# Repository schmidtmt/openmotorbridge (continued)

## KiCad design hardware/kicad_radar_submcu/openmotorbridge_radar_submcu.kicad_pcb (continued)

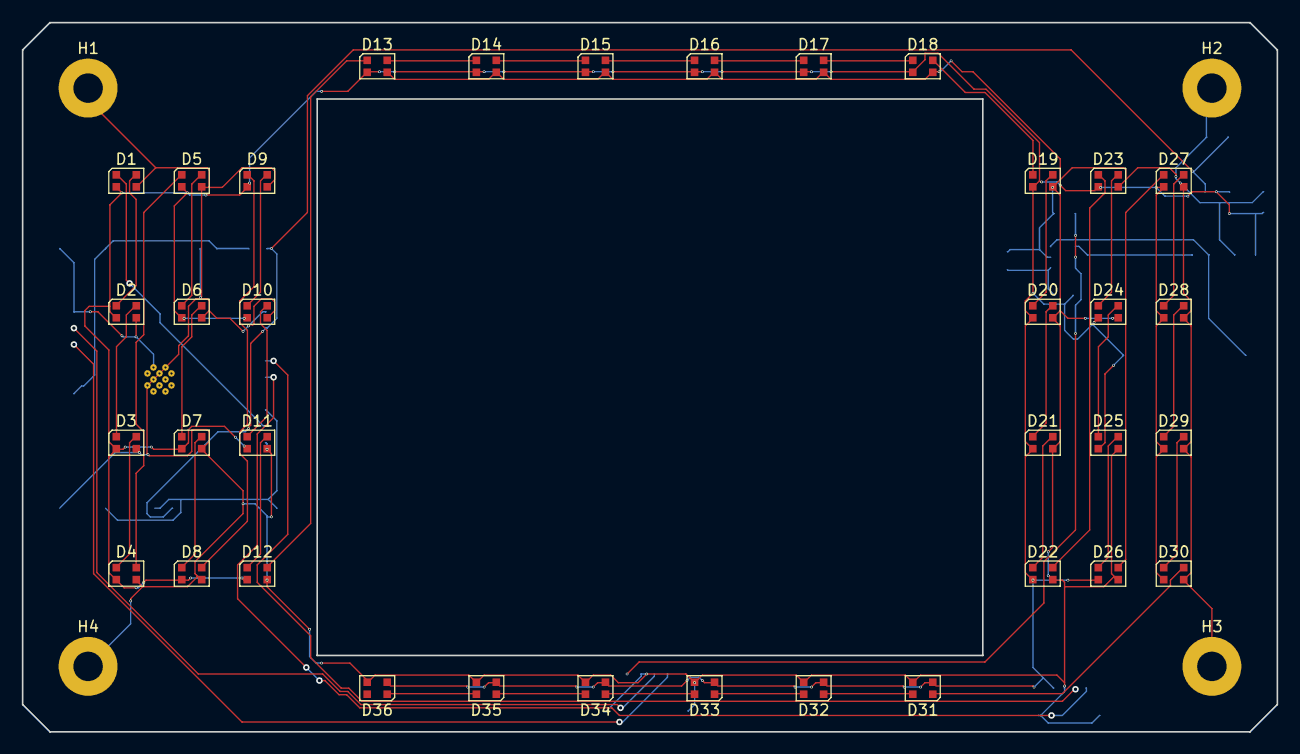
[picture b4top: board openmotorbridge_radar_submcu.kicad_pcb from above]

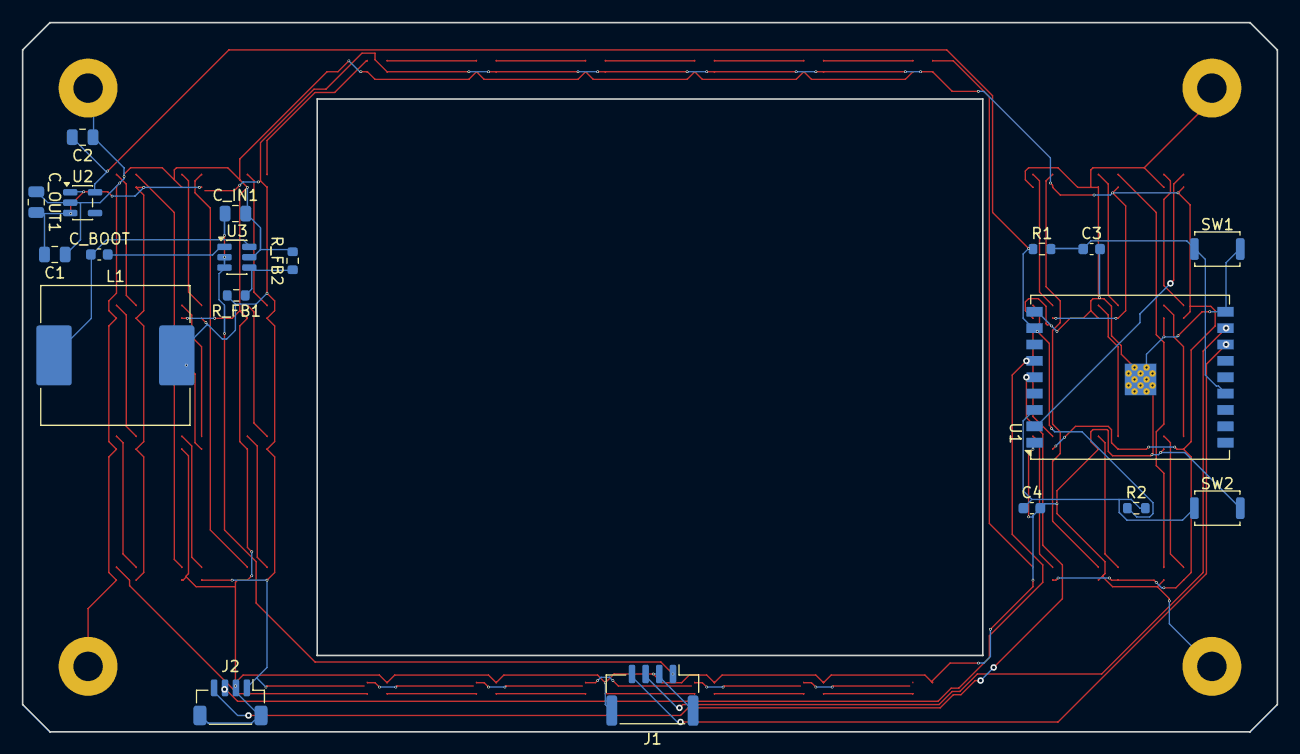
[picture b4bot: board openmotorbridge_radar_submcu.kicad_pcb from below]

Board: 2 copper layers, 115.0 x 65.0 mm, 59 parts (19 on the bottom side), 49 nets.

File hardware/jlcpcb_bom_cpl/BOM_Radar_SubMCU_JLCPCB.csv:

Designator,Comment,Footprint,LCSC Part #,Quantity
C1,10uF_16V,C_0805_2012Metric,,1
C2,10uF_10V,C_0805_2012Metric,,1
"C3, C4",100nF,C_0603_1608Metric,,2
D25,PESD5V0S2BT,SOT-23,,1
"D1, D10, D11, D12, D13, D14, D15, D16, D17, D18, D19, D2, D20, D21, D22, D23, D24, D25, D26, D27, D28, D29, D3, D30, D31, D32, D33, D34, D35, D36, D4, D5, D6, D7, D8, D9",WS2812B-2020,LED_WS2812B-2020_PLCC4_2.0x2.0mm,,36
"H1, H2, H3, H4",M2.5_MountingHole,MountingHole_2.7mm_M2.5_Pad,,4
J1,JST_SH_4P_CENTRAL,JST_SH_SM04B-SRSS-TB_1x04-1MP_P1.00mm_Horizontal,,1
J2,JST_SH_4P_MR20,JST_SH_SM04B-SRSS-TB_1x04-1MP_P1.00mm_Horizontal,,1
J3,U.FL_5G9_V2X,U.FL_Hirose_U.FL-R-SMT-1_Vertical,,1
"R1, R2",10k,R_0603_1608Metric,,2
SW1,BOOT_SW,SW_Push_SPST_NO_Alps_SKRK,,1
SW2,RESET_SW,SW_Push_SPST_NO_Alps_SKRK,,1
U1,ESP32-C5-WROOM-1U,ESP32-C3-WROOM-02U,,1
U2,TPS7A0533,SOT-23-5,,1

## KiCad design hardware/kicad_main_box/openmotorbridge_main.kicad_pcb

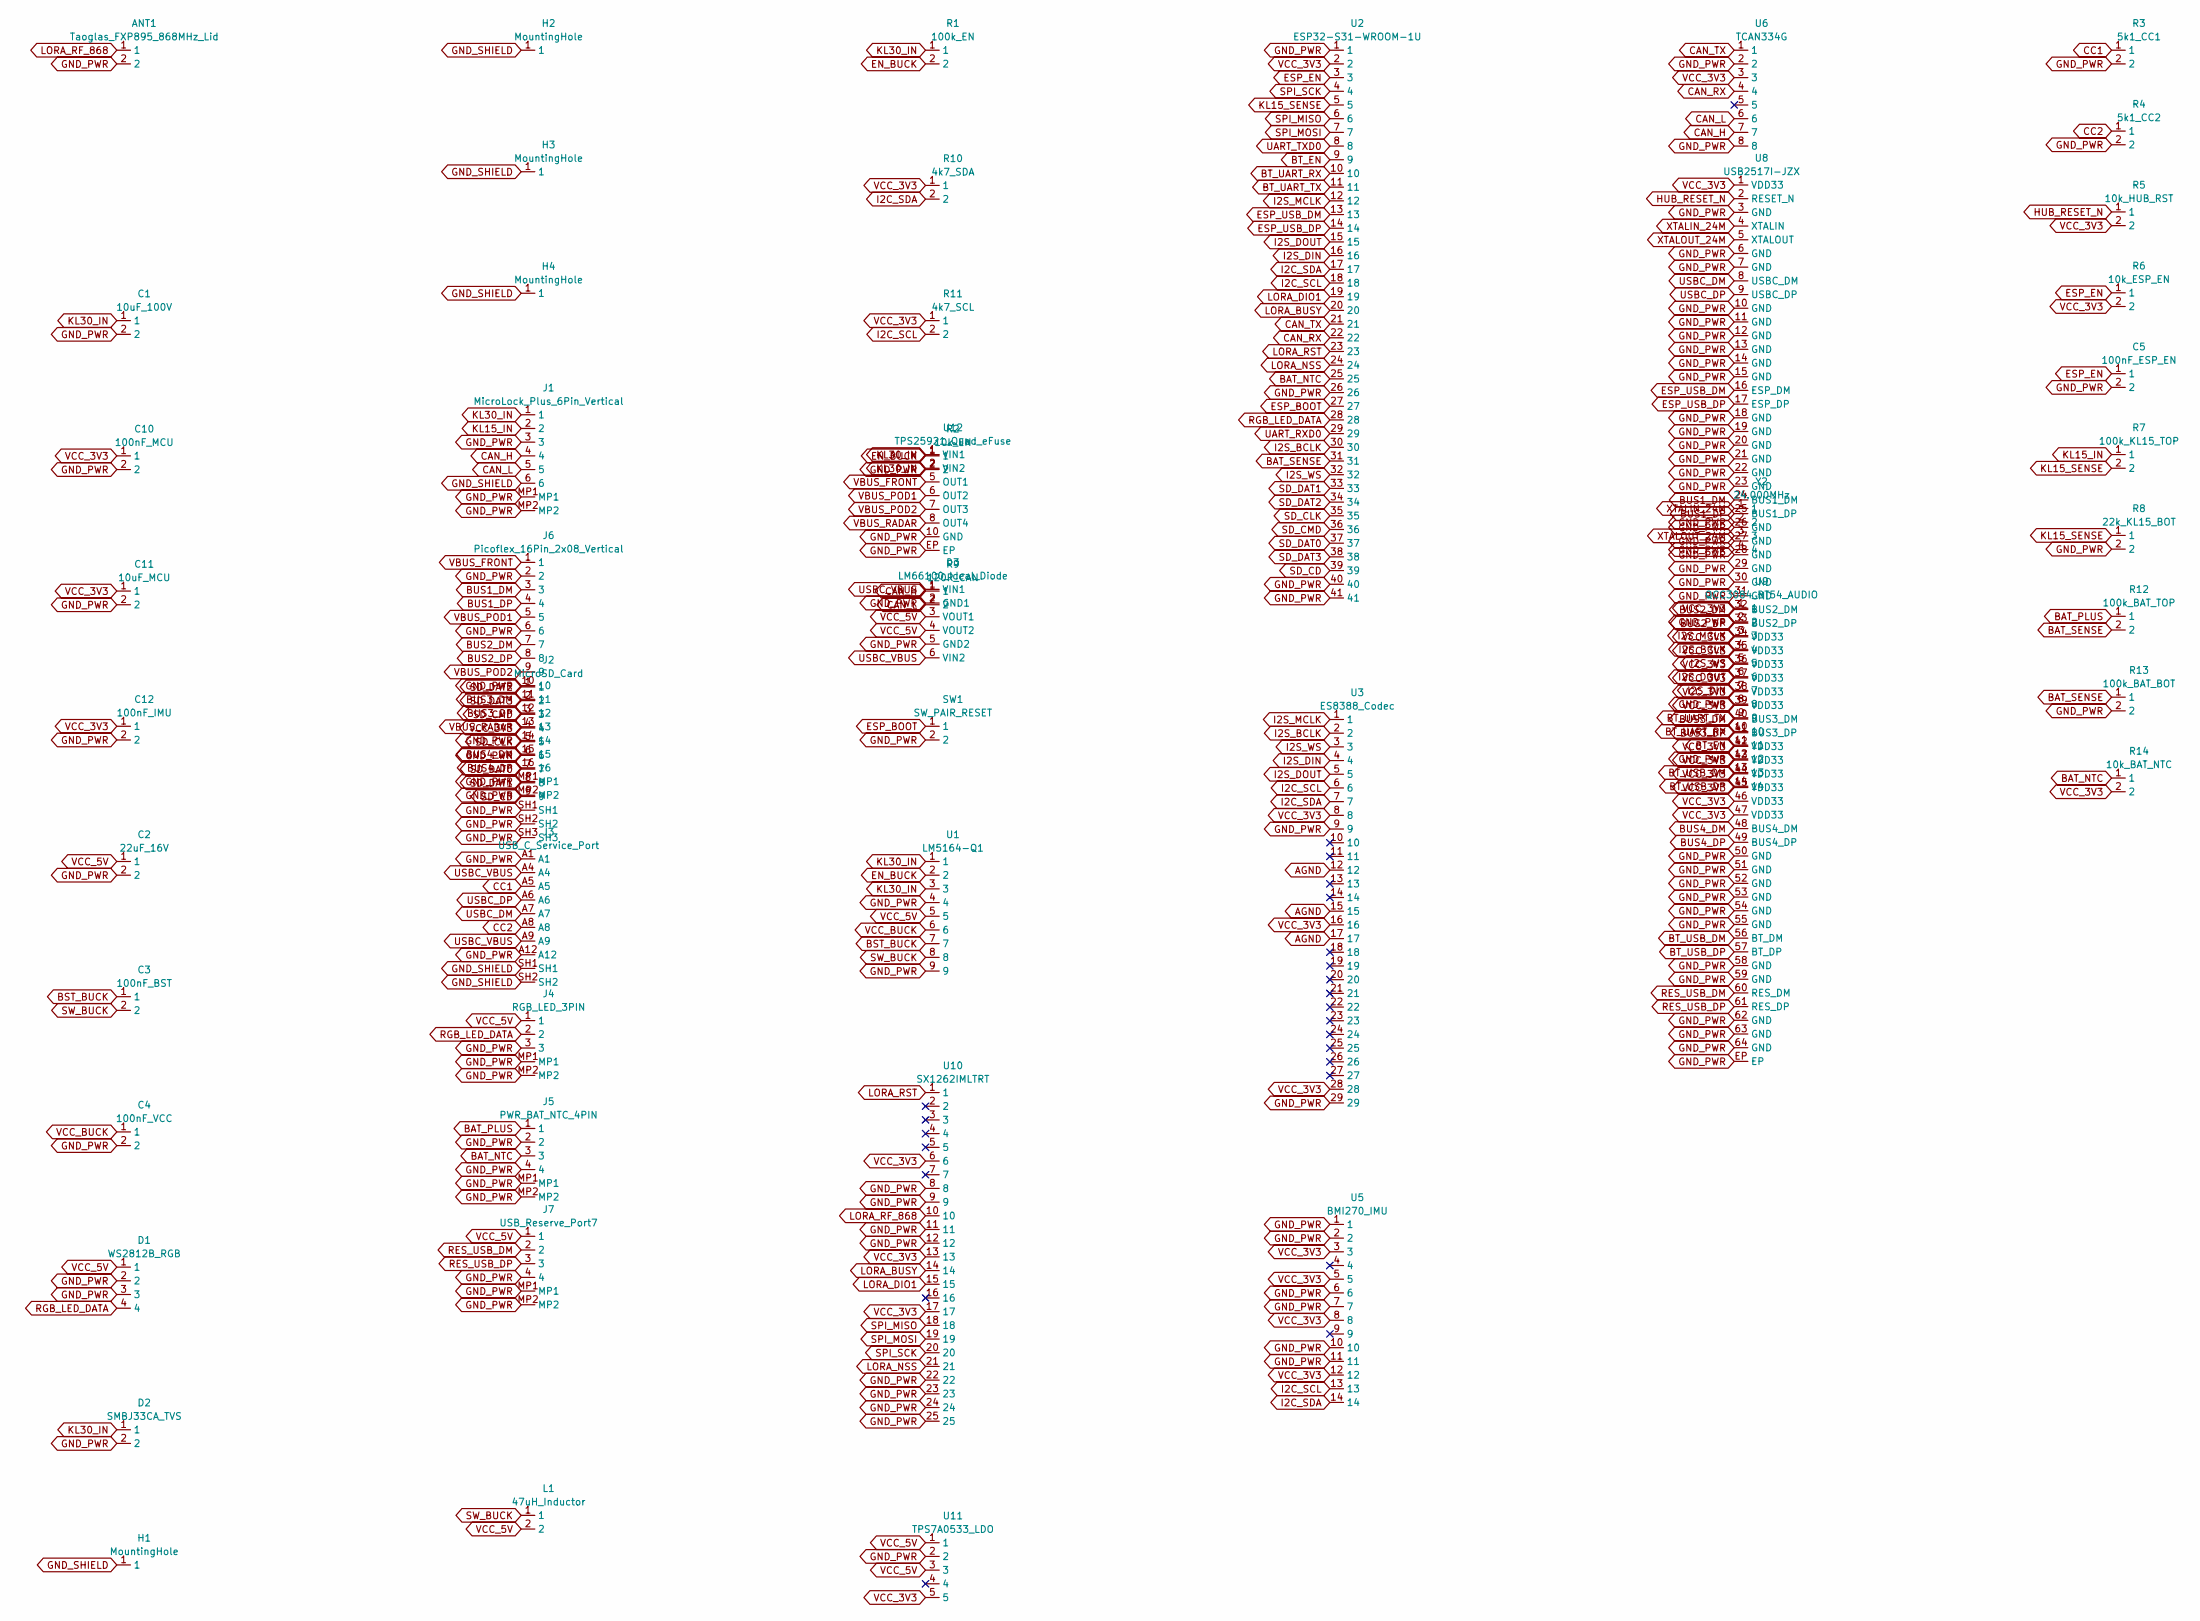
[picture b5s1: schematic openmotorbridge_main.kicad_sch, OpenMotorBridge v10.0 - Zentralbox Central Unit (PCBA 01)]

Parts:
ANT1: Taoglas_FXP895_868MHz_Lid; U.FL_Hirose_U.FL-R-SMT-1_Vertical
C1: 10uF_100V; C_0805_2012Metric
C2: 22uF_16V; C_0805_2012Metric
C3: 100nF_BST; C_0603_1608Metric
C4: 100nF_VCC; C_0603_1608Metric
C5: 100nF_ESP_EN; C_0603_1608Metric
C10: 100nF_MCU; C_0603_1608Metric
C11: 10uF_MCU; C_0805_2012Metric
C12: 100nF_IMU; C_0603_1608Metric
D1: WS2812B_RGB; LED_WS2812B-2020
D2: SMBJ33CA_TVS; D_SMB
D3: LM66100_Ideal_Diode; SOT-23-6
H1, H2, H3, H4: MountingHole; MountingHole_3.2mm_M3_Pad_Via
J1: MicroLock_Plus_6Pin_Vertical; Molex_Micro-Lock_Plus_505568-0671_1x06_P1.25mm_Vertical
J2: MicroSD_Card; microSD_HC_Hirose_DM3D-SF
J3: USB_C_Service_Port; USB_C_Receptacle_HRO_TYPE-C-31-M-12_16P
J4: RGB_LED_3PIN; Molex_Micro-Lock_Plus_505568-0371_1x03_P1.25mm_Vertical
J5: PWR_BAT_NTC_4PIN; Molex_Micro-Lock_Plus_505568-0471_1x04_P1.25mm_Vertical
J6: Picoflex_16Pin_2x08_Vertical; Molex_Picoflex_90814-0016_2x08_P1.27mm_Vertical
J7: USB_Reserve_Port7; Molex_Micro-Lock_Plus_505568-0471_1x04_P1.25mm_Vertical
L1: 47uH_Inductor; L_Sunlord_MWSA1206S-470
R1: 100k_EN; R_0603_1608Metric
R2: 10k_EN; R_0603_1608Metric
R3: 5k1_CC1; R_0603_1608Metric
R4: 5k1_CC2; R_0603_1608Metric
R5: 10k_HUB_RST; R_0603_1608Metric
R6: 10k_ESP_EN; R_0603_1608Metric
R7: 100k_KL15_TOP; R_0603_1608Metric
R8: 22k_KL15_BOT; R_0603_1608Metric
R9: 120R_CAN; R_0603_1608Metric
R10: 4k7_SDA; R_0603_1608Metric
R11: 4k7_SCL; R_0603_1608Metric
R12: 100k_BAT_TOP; R_0603_1608Metric
R13: 100k_BAT_BOT; R_0603_1608Metric
R14: 10k_BAT_NTC; R_0603_1608Metric
SW1: SW_PAIR_RESET; SW_Push_SPST_NO_Alps_SKRK
U1: LM5164-Q1; SOIC-8-1EP_3.9x4.9mm_P1.27mm_EP2.41x3.3mm
U2: ESP32-S31-WROOM-1U; ESP32-S3-WROOM-1U
U3: ES8388_Codec; QFN-28-1EP_4x4mm_P0.4mm_EP2.4x2.4mm
U5: BMI270_IMU; LGA-14_2.5x3mm_P0.5mm
U6: TCAN334G; SOIC-8_3.9x4.9mm_P1.27mm
U8: USB2517I-JZX; QFN-64-1EP_9x9mm_P0.5mm_EP7.15x7.15mm
U9: QCC3084_BT54_AUDIO; Qualcomm_QCC3084_Module
U10: SX1262IMLTRT; QFN-24-1EP_4x4mm_P0.5mm_EP2.8x2.8mm
U11: TPS7A0533_LDO; SOT-23-5
U12: TPS25921_Quad_eFuse; QFN-20-1EP_3.5x4mm_P0.5mm
Y2: 24.000MHz; Crystal_SMD_2016-4Pin_2.0x1.6mm

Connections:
AGND: U3.12, U3.15, U3.17
BAT_NTC: J5.3, R14.1, U2.25
BAT_PLUS: J5.1, R12.1
BAT_SENSE: R12.2, R13.1, U2.31
BST_BUCK: C3.1, U1.7
BT_EN: U2.9, U9.11
BT_UART_RX: U2.10, U9.10
BT_UART_TX: U2.11, U9.9
BT_USB_DM: U8.56 (BT_DM), U9.13
BT_USB_DP: U8.57 (BT_DP), U9.14
BUS1_DM: J6.3, U8.24 (BUS1_DM)
BUS1_DP: J6.4, U8.25 (BUS1_DP)
BUS2_DM: J6.7, U8.32 (BUS2_DM)
BUS2_DP: J6.8, U8.33 (BUS2_DP)
BUS3_DM: J6.11, U8.40 (BUS3_DM)
BUS3_DP: J6.12, U8.41 (BUS3_DP)
BUS4_DM: J6.15, U8.48 (BUS4_DM)
BUS4_DP: J6.16, U8.49 (BUS4_DP)
CAN_H: J1.4, R9.1, U6.7
CAN_L: J1.5, R9.2, U6.6
CAN_RX: U2.22, U6.4
CAN_TX: U2.21, U6.1
CC1: J3.A5, R3.1
CC2: J3.A8, R4.1
EN_BUCK: R1.2, R2.1, U1.2
ESP_BOOT: SW1.1, U2.27
ESP_EN: C5.1, R6.1, U2.3
ESP_USB_DM: U2.13, U8.16 (ESP_DM)
ESP_USB_DP: U2.14, U8.17 (ESP_DP)
GND_PWR: ANT1.2, C1.2, C2.2, C4.2, C5.2, C10.2, C11.2, C12.2, D1.2, D1.3, D2.2, D3.2 (GND1), D3.5 (GND2), J1.3, J1.MP1, J1.MP2, J2.6, J2.SH1, J2.SH2, J2.SH3, J3.A1, J3.A12, J4.3, J4.MP1, J4.MP2, J5.2, J5.4, J5.MP1, J5.MP2, J6.2, J6.6, J6.10, J6.14, J6.MP1, J6.MP2, J7.4, J7.MP1, J7.MP2, R2.2, R3.2, R4.2, R8.2, R13.2, SW1.2, U1.4, U1.9, U2.1, U2.26, U2.40, U2.41, U3.9, U3.29, U5.1, U5.2, U5.6, U5.7, U5.10, U5.11, U6.2, U6.8, U8.3 (GND), U8.6 (GND), U8.7 (GND), U8.10 (GND), U8.11 (GND), U8.12 (GND), U8.13 (GND), U8.14 (GND), U8.15 (GND), U8.18 (GND), U8.19 (GND), U8.20 (GND), U8.21 (GND), U8.22 (GND), U8.23 (GND), U8.26 (GND), U8.27 (GND), U8.28 (GND), U8.29 (GND), U8.30 (GND), U8.31 (GND), U8.50 (GND), U8.51 (GND), U8.52 (GND), U8.53 (GND), U8.54 (GND), U8.55 (GND), U8.58 (GND), U8.59 (GND), U8.62 (GND), U8.63 (GND), U8.64 (GND), U8.EP, U9.2, U9.8, U9.12, U10.8, U10.9, U10.11, U10.12, U10.22, U10.23, U10.24, U10.25, U11.2, U12.10 (GND), U12.EP, Y2.2, Y2.4
GND_SHIELD: H1.1, H2.1, H3.1, H4.1, J1.6, J3.SH1, J3.SH2
HUB_RESET_N: R5.1, U8.2 (RESET_N)
I2C_SCL: R11.2, U2.18, U3.6, U5.13
I2C_SDA: R10.2, U2.17, U3.7, U5.14
I2S_BCLK: U2.30, U3.2, U9.4
I2S_DIN: U2.16, U3.4, U9.7
I2S_DOUT: U2.15, U3.5, U9.6
I2S_MCLK: U2.12, U3.1, U9.3
I2S_WS: U2.32, U3.3, U9.5
KL15_IN: J1.2, R7.1
KL15_SENSE: R7.2, R8.1, U2.5
KL30_IN: C1.1, D2.1, J1.1, R1.1, U1.1, U1.3, U12.1 (VIN1), U12.2 (VIN2)
LORA_BUSY: U2.20, U10.14
LORA_DIO1: U2.19, U10.15
LORA_NSS: U2.24, U10.21
LORA_RF_868: ANT1.1, U10.10
LORA_RST: U2.23, U10.1
RES_USB_DM: J7.2, U8.60 (RES_DM)
RES_USB_DP: J7.3, U8.61 (RES_DP)
RGB_LED_DATA: D1.4, J4.2, U2.28
SD_CD: J2.9, U2.39
SD_CLK: J2.5, U2.35
SD_CMD: J2.3, U2.36
SD_DAT0: J2.7, U2.37
SD_DAT1: J2.8, U2.33
SD_DAT2: J2.1, U2.34
SD_DAT3: J2.2, U2.38
SPI_MISO: U2.6, U10.18
SPI_MOSI: U2.7, U10.19
SPI_SCK: U2.4, U10.20
SW_BUCK: C3.2, L1.1, U1.8
UART_RXD0: U2.29
UART_TXD0: U2.8
USBC_DM: J3.A7, U8.8 (USBC_DM)
USBC_DP: J3.A6, U8.9 (USBC_DP)
USBC_VBUS: D3.1 (VIN1), D3.6 (VIN2), J3.A4, J3.A9
VBUS_FRONT: J6.1, U12.5 (OUT1)
VBUS_POD1: J6.5, U12.6 (OUT2)
VBUS_POD2: J6.9, U12.7 (OUT3)
VBUS_RADAR: J6.13, U12.8 (OUT4)
VCC_3V3: C10.1, C11.1, C12.1, J2.4, R5.2, R6.2, R10.1, R11.1, R14.2, U2.2, U3.8, U3.16, U3.28, U5.3, U5.5, U5.8, U5.12, U6.3, U8.1 (VDD33), U8.34 (VDD33), U8.35 (VDD33), U8.36 (VDD33), U8.37 (VDD33), U8.38 (VDD33), U8.39 (VDD33), U8.42 (VDD33), U8.43 (VDD33), U8.44 (VDD33), U8.45 (VDD33), U8.46 (VDD33), U8.47 (VDD33), U9.1, U10.6, U10.13, U10.17, U11.5
VCC_5V: C2.1, D1.1, D3.3 (VOUT1), D3.4 (VOUT2), J4.1, J7.1, L1.2, U1.5, U11.1, U11.3
VCC_BUCK: C4.1, U1.6
XTALIN_24M: U8.4 (XTALIN), Y2.1
XTALOUT_24M: U8.5 (XTALOUT), Y2.3

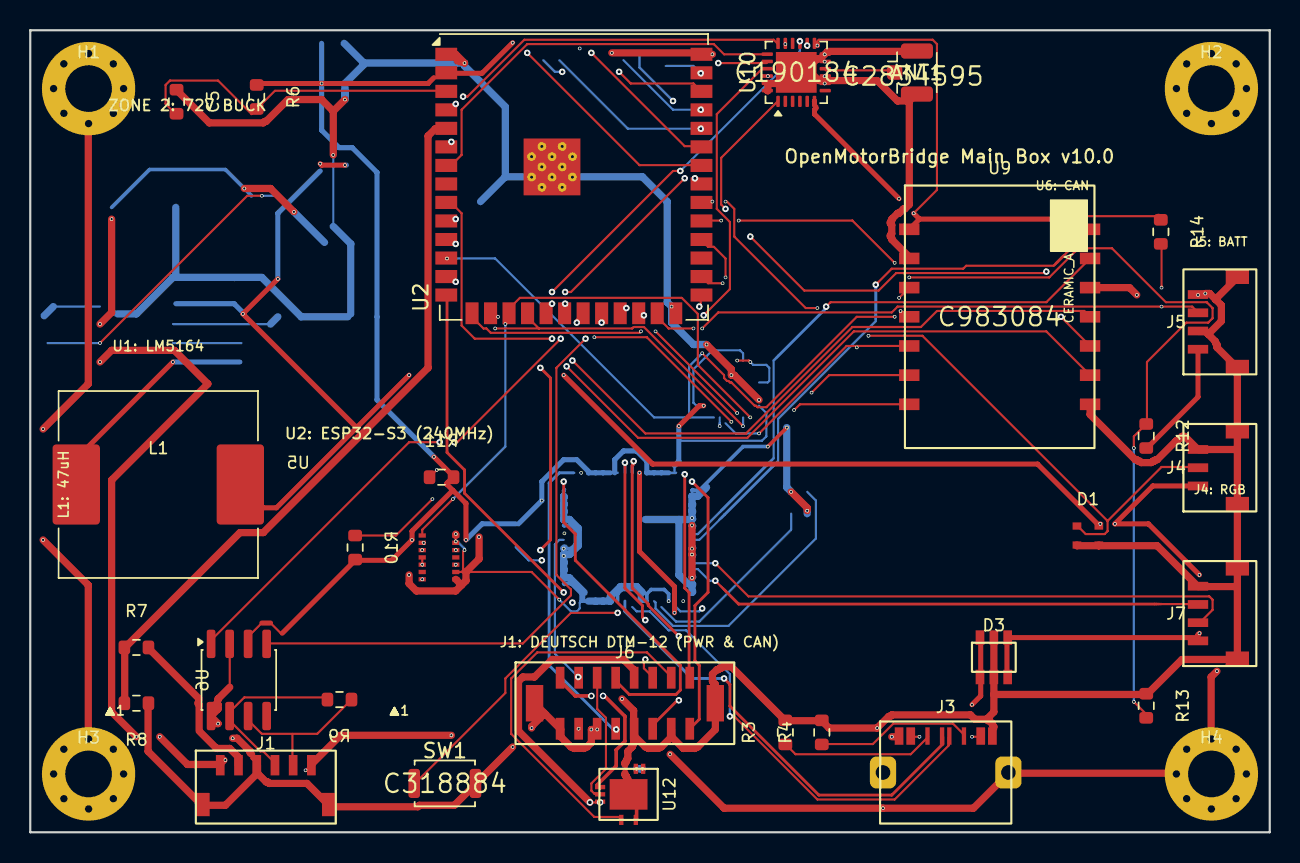
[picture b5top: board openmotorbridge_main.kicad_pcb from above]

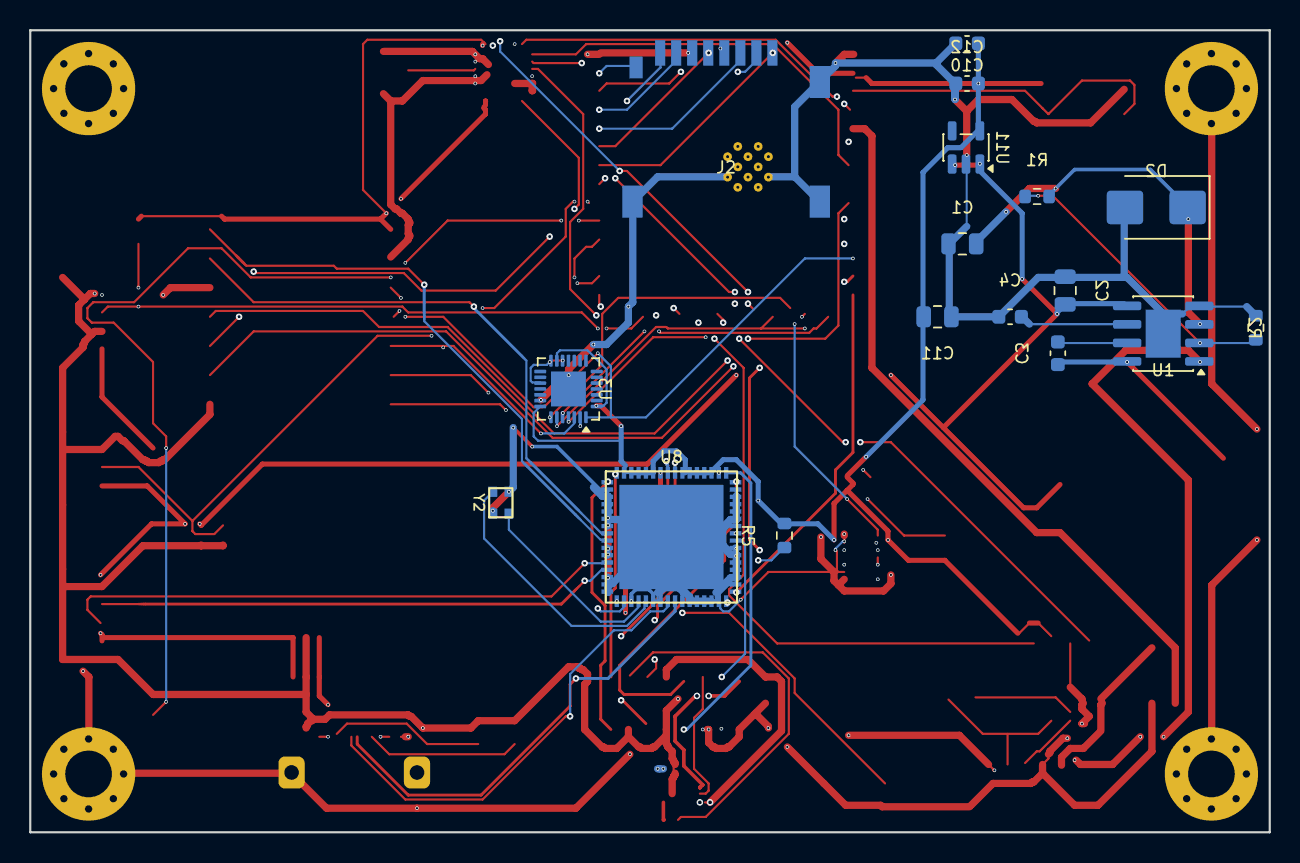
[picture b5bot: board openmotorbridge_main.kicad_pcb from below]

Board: 4 copper layers, 85.0 x 55.0 mm, 50 parts (17 on the bottom side), 73 nets.

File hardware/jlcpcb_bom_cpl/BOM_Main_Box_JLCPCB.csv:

Designator,Comment,Footprint,LCSC Part #,Quantity
ANT1,Taoglas_FXP895_868MHz_Lid,U.FL_Hirose_U.FL-R-SMT-1_Vertical,C2834595,1
ANT2,Taoglas_FXUWB10_6.5GHz_Ch5_Floor,U.FL_Hirose_U.FL-R-SMT-1_Vertical,C2834595,1
C1,10uF_100V,Capacitor_SMD:C_0805_2012Metric,,1
C10,100nF_MCU,Capacitor_SMD:C_0603_1608Metric,,1
C11,10uF_MCU,Capacitor_SMD:C_0805_2012Metric,,1
C12,100nF_IMU,Capacitor_SMD:C_0603_1608Metric,,1
C2,22uF_16V,Capacitor_SMD:C_0805_2012Metric,,1
C3,100nF_BST,Capacitor_SMD:C_0603_1608Metric,,1
C4,100nF_VCC,Capacitor_SMD:C_0603_1608Metric,,1
C6,1uF_POD1,Capacitor_SMD:C_0603_1608Metric,,1
C7,1uF_POD2,Capacitor_SMD:C_0603_1608Metric,,1
D1,WS2812B_RGB,LED_SMD:LED_WS2812B-2020,,1
D2,SMBJ33CA_TVS,Diode_SMD:D_SMB,,1
"H1, H2, H3, H4",,MountingHole:MountingHole_3.2mm_M3_Pad_Via,,4
J1,DEUTSCH_DTM12_HEADER,Connector_IDC:IDC-Header_2x13_P2.54mm_Vertical,C2934175,1
J2,MicroSD_Card,Connector_Card:microSD_HC_Molex_47571-0001,,1
J3,USB2_IDC_HEADER_9PIN,Connector_IDC:IDC-Header_2x05_P2.54mm_Vertical,,1
J4,RGB_LED_3PIN,Connector_JST:JST_PH_B3B-PH-K_1x03_P2.00mm_Vertical,,1
J5,PWR_BAT_NTC_4PIN,Connector_JST:JST_PH_B4B-PH-K_1x04_P2.00mm_Vertical,,1
L1,47uH_Inductor,Inductor_SMD:L_Sunlord_MWSA1206S-470,,1
R1,100k_EN,Resistor_SMD:R_0603_1608Metric,,1
R10,4k7_SDA,Resistor_SMD:R_0603_1608Metric,,1
R11,4k7_SCL,Resistor_SMD:R_0603_1608Metric,,1
R2,10k_EN,Resistor_SMD:R_0603_1608Metric,,1
R5,600R_POD1,Resistor_SMD:R_0603_1608Metric,,1
R6,600R_POD2,Resistor_SMD:R_0603_1608Metric,,1
R9,120R_CAN,Resistor_SMD:R_0603_1608Metric,,1
SW1,SW_PAIR_RESET,SW_Push_SPST_NO_Alps_SKRK,C318884,1
U1,LM5164-Q1,Package_SO:SOIC-8-1EP_3.9x4.9mm_P1.27mm_EP2.41x3.3mm,,1
U2,ESP32-S3-WROOM-1U-N16R8,ESP32-S3-WROOM-1U,,1
U3,ES8388_Codec,Package_DFN_QFN:QFN-28-1EP_4x4mm_P0.4mm_EP2.4x2.4mm,,1
U5,BMI270_IMU,Package_LGA:LGA-14_2.5x3mm_P0.5mm,,1
U6,TCAN334G,Package_SO:SOIC-8_3.9x4.9mm_P1.27mm,,1
U7,SX1262IMLTRT,QFN-24-1EP_4x4mm_P0.5mm_EP2.8x2.8mm,C190184,1
U8,DW3110,QFN-16-1EP_3x3mm_P0.5mm_EP1.7x1.7mm_ThermalVias,C2934600,1
U9,TPS7A0533_LDO,Package_TO_SOT_SMD:SOT-23-5,,1

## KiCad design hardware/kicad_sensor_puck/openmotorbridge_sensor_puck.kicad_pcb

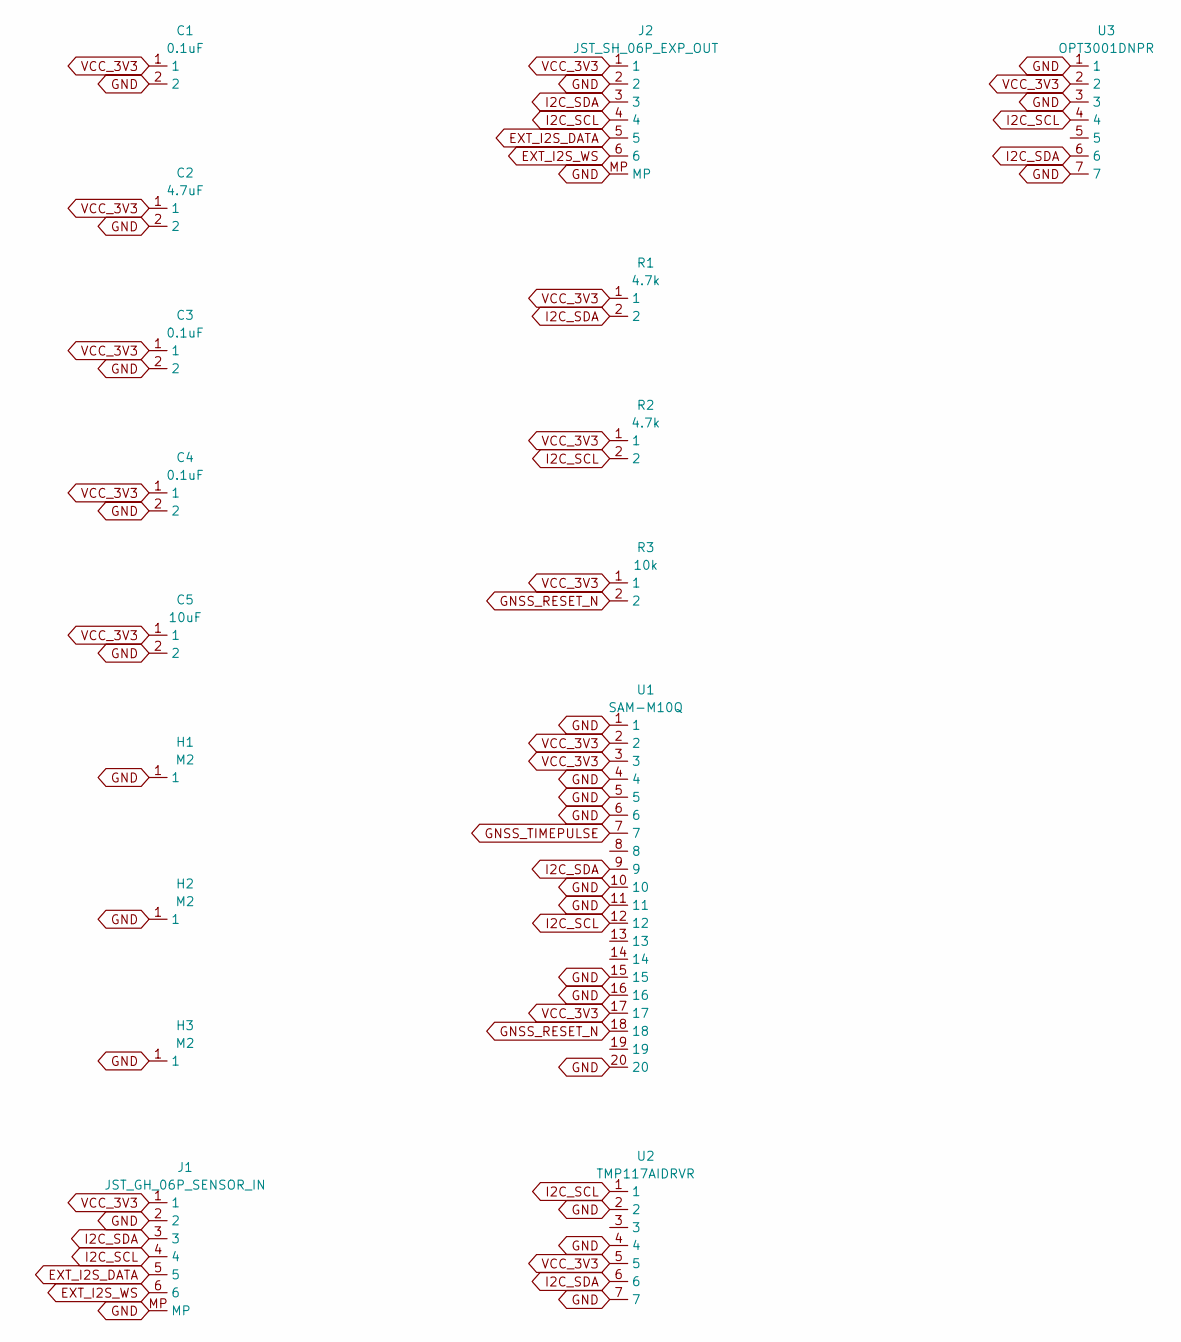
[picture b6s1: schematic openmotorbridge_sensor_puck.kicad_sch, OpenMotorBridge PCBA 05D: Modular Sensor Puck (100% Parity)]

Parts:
C1, C3, C4: 0.1uF; C_0603_1608Metric
C2: 4.7uF; C_0603_1608Metric
C5: 10uF; C_0603_1608Metric
H1, H2, H3: M2; MountingHole_2.2mm_M2_Pad
J1: JST_GH_06P_SENSOR_IN; JST_GH_SM06B-GHS-TB_1x06-1MP_P1.25mm_Horizontal
J2: JST_SH_06P_EXP_OUT; JST_SH_SM06B-SRSS-TB_1x06-1MP_P1.00mm_Horizontal
R1, R2: 4.7k; R_0603_1608Metric
R3: 10k; R_0603_1608Metric
U1: SAM-M10Q; ublox_SAM-M8Q
U2: TMP117AIDRVR; WSON-6-1EP_2x2mm_P0.65mm_EP1x1.6mm
U3: OPT3001DNPR; WSON-6-1EP_2x2mm_P0.65mm_EP1x1.6mm

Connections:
EXT_I2S_DATA: J1.5, J2.5
EXT_I2S_WS: J1.6, J2.6
GND: C1.2, C2.2, C3.2, C4.2, C5.2, H1.1, H2.1, H3.1, J1.2, J1.MP, J2.2, J2.MP, U1.1, U1.4, U1.5, U1.6, U1.10, U1.11, U1.15, U1.16, U1.20, U2.2, U2.4, U2.7, U3.1, U3.3, U3.7
GNSS_RESET_N: R3.2, U1.18
GNSS_TIMEPULSE: U1.7
I2C_SCL: J1.4, J2.4, R2.2, U1.12, U2.1, U3.4
I2C_SDA: J1.3, J2.3, R1.2, U1.9, U2.6, U3.6
VCC_3V3: C1.1, C2.1, C3.1, C4.1, C5.1, J1.1, J2.1, R1.1, R2.1, R3.1, U1.2, U1.3, U1.17, U2.5, U3.2

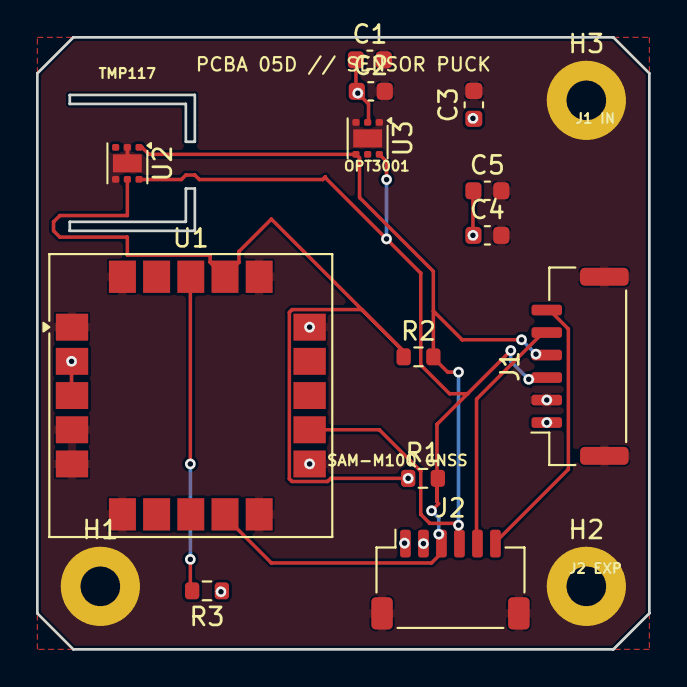
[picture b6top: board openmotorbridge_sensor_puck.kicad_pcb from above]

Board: 4 copper layers, 34.0 x 34.0 mm, 16 parts (0 on the bottom side), 7 nets.

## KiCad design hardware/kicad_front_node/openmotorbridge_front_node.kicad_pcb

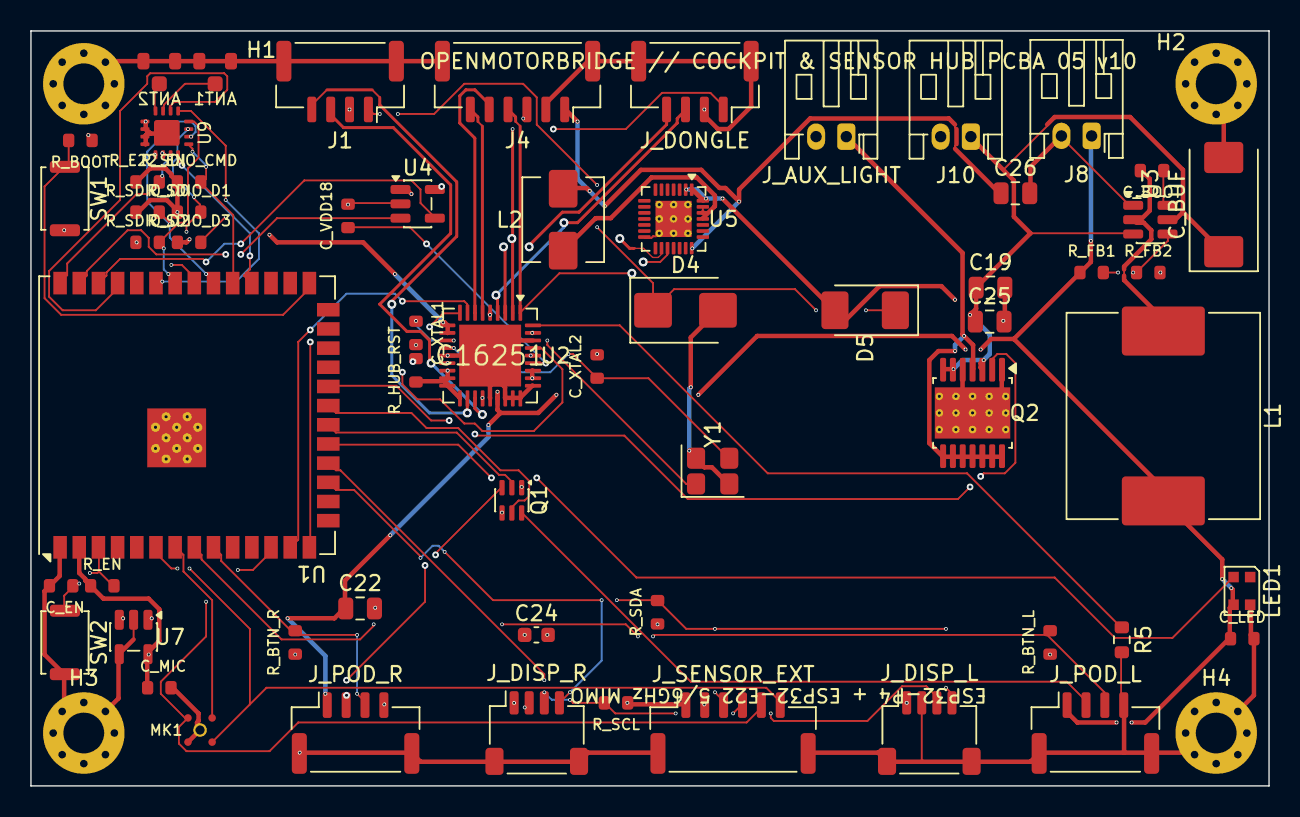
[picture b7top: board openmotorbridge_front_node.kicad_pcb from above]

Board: 4 copper layers, 82.0 x 50.0 mm, 64 parts (0 on the bottom side), 54 nets.

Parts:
ANT1: U.FL_5_6GHZ_MAIN; U.FL_Hirose_U.FL-R-SMT-1_Vertical
ANT2: U.FL_5_6GHZ_MIMO; U.FL_Hirose_U.FL-R-SMT-1_Vertical
C19: 10uF_50V; C_0805_2012Metric
C22: 22uF_16V; C_0805_2012Metric
C24: 2.2uF_3V3; C_0603_1608Metric
C25: 10uF_50V_PD1; C_0805_2012Metric
C26: 22uF_25V_PD1; C_0805_2012Metric
C_BOOT: 100nF; C_0603_1608Metric
C_BUF: 470uF_25V_POLYMER; CP_EIA-7343-31_Kemet-D
C_EN: 1uF; C_0603_1608Metric
C_LED: 100nF; C_0603_1608Metric
C_MIC: 100nF; C_0603_1608Metric
C_VDD18: 1uF; C_0603_1608Metric
C_XTAL1, C_XTAL2: 18pF; C_0603_1608Metric
D4: SMCJ36CA_TVS; D_SMB
D5: SS34_REV_POL; D_SMA
H1, H2, H3, H4: M2.5_MOUNT; MountingHole_2.7mm_M2.5_Pad_Via
J1: JST_GH_04P_BACKBONE; JST_GH_SM04B-GHS-TB_1x04-1MP_P1.25mm_Horizontal
J4: JST_GH_06P_HUB_EXT; JST_GH_SM06B-GHS-TB_1x06-1MP_P1.25mm_Horizontal
J8: JST_PH_02P_CAM_PWR; JST_PH_S2B-PH-K_1x02_P2.00mm_Horizontal
J10: JST_PH_02P_NAVI_PWR; JST_PH_S2B-PH-K_1x02_P2.00mm_Horizontal
J_AUX_LIGHT: JST_PH_02P_AUX_LIGHT; JST_PH_S2B-PH-K_1x02_P2.00mm_Horizontal
J_DISP_L: JST_SH_04P_DISP_L; JST_SH_SM04B-SRSS-TB_1x04-1MP_P1.00mm_Horizontal
J_DISP_R: JST_SH_04P_DISP_R; JST_SH_SM04B-SRSS-TB_1x04-1MP_P1.00mm_Horizontal
J_DONGLE: JST_GH_04P_DONGLE; JST_GH_SM04B-GHS-TB_1x04-1MP_P1.25mm_Horizontal
J_POD_L: JST_GH_04P_POD_L; JST_GH_SM04B-GHS-TB_1x04-1MP_P1.25mm_Horizontal
J_POD_R: JST_GH_04P_POD_R; JST_GH_SM04B-GHS-TB_1x04-1MP_P1.25mm_Horizontal
J_SENSOR_EXT: JST_GH_06P_SENSOR_PUCK; JST_GH_SM06B-GHS-TB_1x06-1MP_P1.25mm_Horizontal
L1: 4.7uH_Power_Choke; L_Sunlord_MWSA1206S-470
L2: 4.7uH_PD1_Choke; L_Sunlord_MWSA0503S
LED1: WS2812B-2020_RGB; LED_WS2812B-2020_PLCC4_2.0x2.0mm
MK1: SPH0645LM4H; Knowles_SPH0645LM4H
Q1: DMN63D8_BSD_MOSFET; SOT-363_SC-70-6
Q2: TPS1H100_AUX_LIGHT; Texas_HTSSOP-14-1EP_4.4x5mm_P0.65mm_EP3.4x5mm_Mask3.155x3.2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
R5: 12k_RBIAS; R_0603_1608Metric
R_BOOT: 10k; R_0603_1608Metric
R_BTN_L: 10k; R_0603_1608Metric
R_BTN_R: 10k; R_0603_1608Metric
R_E22_EN: 10k; R_0603_1608Metric
R_EN: 10k; R_0603_1608Metric
R_FB1: 100k; R_0603_1608Metric
R_FB2: 13.7k; R_0603_1608Metric
R_HUB_RST: 10k; R_0603_1608Metric
R_SCL: 4.7k; R_0603_1608Metric
R_SDA: 4.7k; R_0603_1608Metric
R_SDIO_CMD: 10k; R_0603_1608Metric
R_SDIO_D0, R_SDIO_D1, R_SDIO_D2, R_SDIO_D3: 10k; R_0603_1608Metric
SW1: BOOT; SW_Push_SPST_NO_Alps_SKRK
SW2: RESET; SW_Push_SPST_NO_Alps_SKRK
U1: ESP32-P4-NR16; ESP32-S3-WROOM-1U
U2: USB2514Bi-AEZG; QFN-36-1EP_6x6mm_P0.5mm_EP4.1x4.1mm
U3: TPS54302_5V_BUCK; SOT-23-6
U4: TPS2051B_PORT2_GATE; SOT-23-5
U5: SW3526_USB_PD1_30W; QFN-28-1EP_4x4mm_P0.4mm_EP2.4x2.4mm_ThermalVias
U7: TLV75533P_3V3_LDO; SOT-23-5
U9: ESP32-E22-WROOM-2X2; QFN-16-1EP_3x3mm_P0.5mm_EP1.7x1.7mm_ThermalVias
Y1: 24.000MHz; Crystal_SMD_3225-4Pin_3.2x2.5mm

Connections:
+12V_AUX: J_AUX_LIGHT.1, Q2.4, Q2.8, Q2.9, Q2.10, Q2.11, Q2.12, Q2.13, Q2.14
+12V_PROT: C19.1, C25.1, C_BUF.1, D5.2, J10.1, Q2.3, Q2.6, Q2.7, U3.3, U3.5, U5.1, U5.2, U5.28
AUX_LIGHT_EN: Q2.2, U1.22
BOOT_5V: C_BOOT.1, U3.6
BSD_LED_LEFT: Q1.2, U1.20
BSD_LED_L_N: J_POD_L.2, Q1.6
BSD_LED_RIGHT: Q1.5, U1.21
BSD_LED_R_N: J_POD_R.2, Q1.3
BTN_SIG_L_N: J_POD_L.3, R_BTN_L.2, U1.8
BTN_SIG_R_N: J_POD_R.3, R_BTN_R.2, U1.9
CP2AA_FAULT_N: U1.38, U4.4
CP2AA_PWR_EN: U1.39, U4.3
E22_EN: R_E22_EN.2, U1.40, U9.3
E22_IRQ: U1.37, U9.10
E22_RF_MAIN: ANT1.1, U9.11
E22_RF_MIMO: ANT2.1, U9.12
ESP_BOOT: R_BOOT.2, SW1.1, U1.27
ESP_EN: C_EN.1, R_EN.2, SW2.1, U1.3
FB_5V: R_FB1.2, R_FB2.1, U3.4
GND: ANT1.2, ANT2.2, C19.2, C22.2, C24.2, C25.2, C26.2, C_BUF.2, C_EN.2, C_LED.2, C_MIC.2, C_VDD18.2, C_XTAL1.2, C_XTAL2.2, D4.2, H1.1, H2.1, H3.1, H4.1, J1.2, J1.MP, J4.2, J4.MP, J8.2, J10.2, J_AUX_LIGHT.2, J_DISP_L.2, J_DISP_L.MP, J_DISP_R.2, J_DISP_R.MP, J_DONGLE.2, J_DONGLE.MP, J_POD_L.4, J_POD_L.MP, J_POD_R.4, J_POD_R.MP, J_SENSOR_EXT.2, J_SENSOR_EXT.MP, LED1.4, MK1.4, MK1.5, Q1.1, Q1.4, Q2.1, Q2.5, Q2.15, R5.2, R_FB2.2, SW1.2, SW2.2, U1.1, U1.41, U2.14, U2.23, U2.25, U2.26, U2.27, U2.28, U2.34, U2.37, U3.1, U4.2, U5.14, U5.29, U7.2, U7.4, U9.2, U9.13, U9.14, U9.15, U9.16, U9.17, Y1.2, Y1.4
HUB_RBIAS: R5.1, U2.36
HUB_RESET_N: R_HUB_RST.2, U2.33
I2C_SCL: J_DISP_L.3, J_DISP_R.3, J_SENSOR_EXT.4, R_SCL.2, U1.18
I2C_SDA: J_DISP_L.4, J_DISP_R.4, J_SENSOR_EXT.3, R_SDA.2, U1.17
MIC_I2S_BCLK: MK1.2, U1.7
MIC_I2S_DATA: J_SENSOR_EXT.5, MK1.1, U1.12
MIC_I2S_WS: J_SENSOR_EXT.6, MK1.3, U1.6
SDIO_CLK: U1.30, U9.4
SDIO_CMD: R_SDIO_CMD.2, U1.31, U9.5
SDIO_D0: R_SDIO_D0.2, U1.32, U9.6
SDIO_D1: R_SDIO_D1.2, U1.33, U9.7
SDIO_D2: R_SDIO_D2.2, U1.34, U9.8
SDIO_D3: R_SDIO_D3.2, U1.35, U9.9
SW_BUCK: C_BOOT.2, L1.1, U3.2
SW_PD1_BUCK: L2.1, U5.25, U5.26, U5.27
USB_DN1_DM: J4.4, U2.1, U5.17
USB_DN1_DP: J4.3, U2.2, U5.16
USB_DN2_DM: J_DONGLE.4, U2.3
USB_DN2_DP: J_DONGLE.3, U2.4
USB_DN3_DM: J4.6, U2.6
USB_DN3_DP: J4.5, U2.7
USB_HS_DM: U1.13, U2.8
USB_HS_DP: U1.14, U2.9
USB_UP_DM: J1.4, U2.20
USB_UP_DP: J1.3, U2.21
VBUS_PD1_OUT: C26.1, J4.1, L2.2, U5.21
VCC_3V3: C24.1, C_MIC.1, J_DISP_L.1, J_DISP_R.1, J_SENSOR_EXT.1, R_BOOT.1, R_BTN_L.1, R_BTN_R.1, R_E22_EN.1, R_EN.1, R_HUB_RST.1, R_SCL.1, R_SDA.1, R_SDIO_CMD.1, R_SDIO_D0.1, R_SDIO_D1.1, R_SDIO_D2.1, R_SDIO_D3.1, U1.2, U2.5, U2.10, U2.11, U2.15, U2.16, U2.17, U2.18, U2.19, U2.22, U2.29, U2.30, U2.32, U2.35, U7.5, U9.1
VCC_5V: C22.1, C_LED.1, J8.1, J_POD_L.1, J_POD_R.1, L1.2, LED1.3, R_FB1.1, U2.24, U4.1, U7.1, U7.3
VCC_5V_DONGLE: J_DONGLE.1, U4.5
VDD18_CORE: C_VDD18.1, U2.31
VIN_60W: D4.1, D5.1, J1.1
WS2812B_DIN: LED1.2, U1.19
XTAL_IN: C_XTAL1.1, U2.12, Y1.1
XTAL_OUT: C_XTAL2.1, U2.13, Y1.3
